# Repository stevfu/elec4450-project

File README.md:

# Custom Buck Converter 
My group designed a unidirectional buck converter with an active low-pass filter and control using a C2000 microcontroller.

The following specifications for this converter are: 

$$
V_i = 36\text{V} - 50\text{V}
$$

$$
V_o = 30\text{V}
$$

$$
f_{sw} = 10\text{kHz}
$$

$$
\Delta I_L = 0.3 I_L
$$

$$
\Delta V_o = 0.005 V_o
$$

The layout, schematic and PCB design of the buck converter was done in KiCAD.

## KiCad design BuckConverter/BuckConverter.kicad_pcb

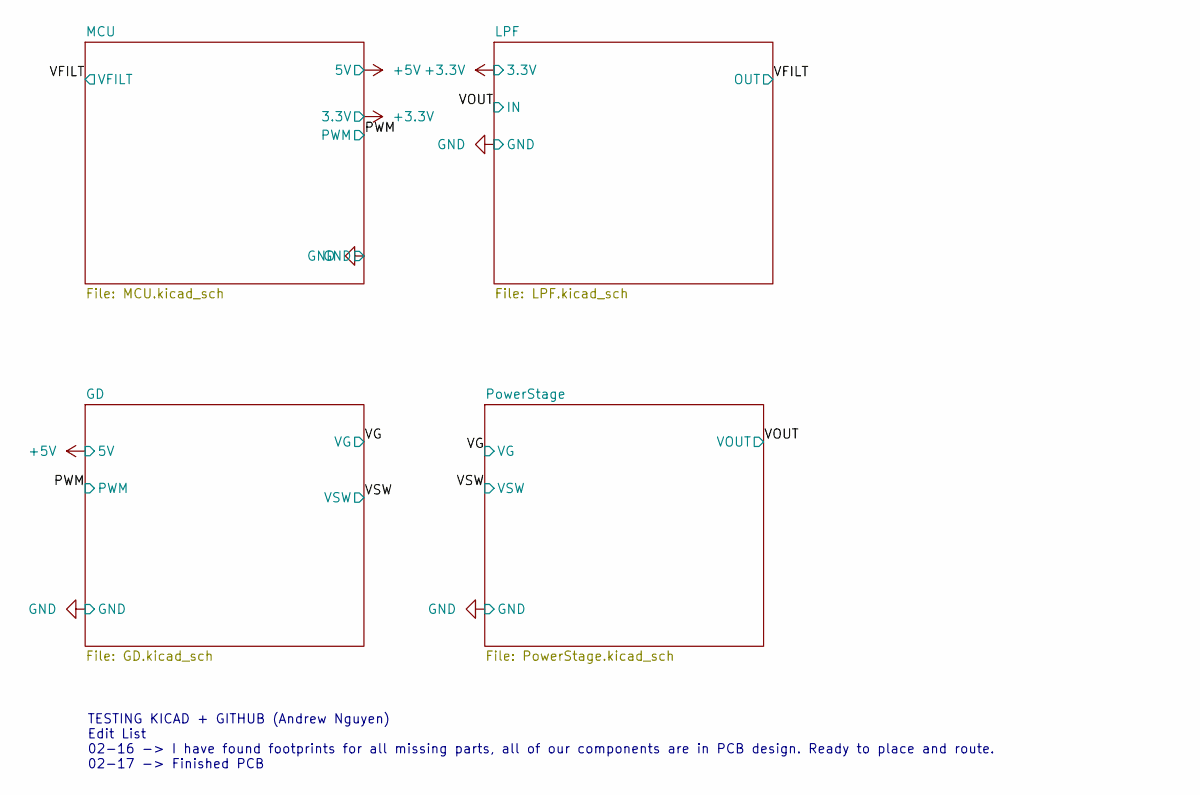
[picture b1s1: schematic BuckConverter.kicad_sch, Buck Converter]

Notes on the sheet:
TESTING KICAD + GITHUB (Andrew Nguyen) Edit List 02-16 -> I have found footprints for all missing parts, all of our components are in PCB design. Ready to place and route. 02-17 -> Finished PCB

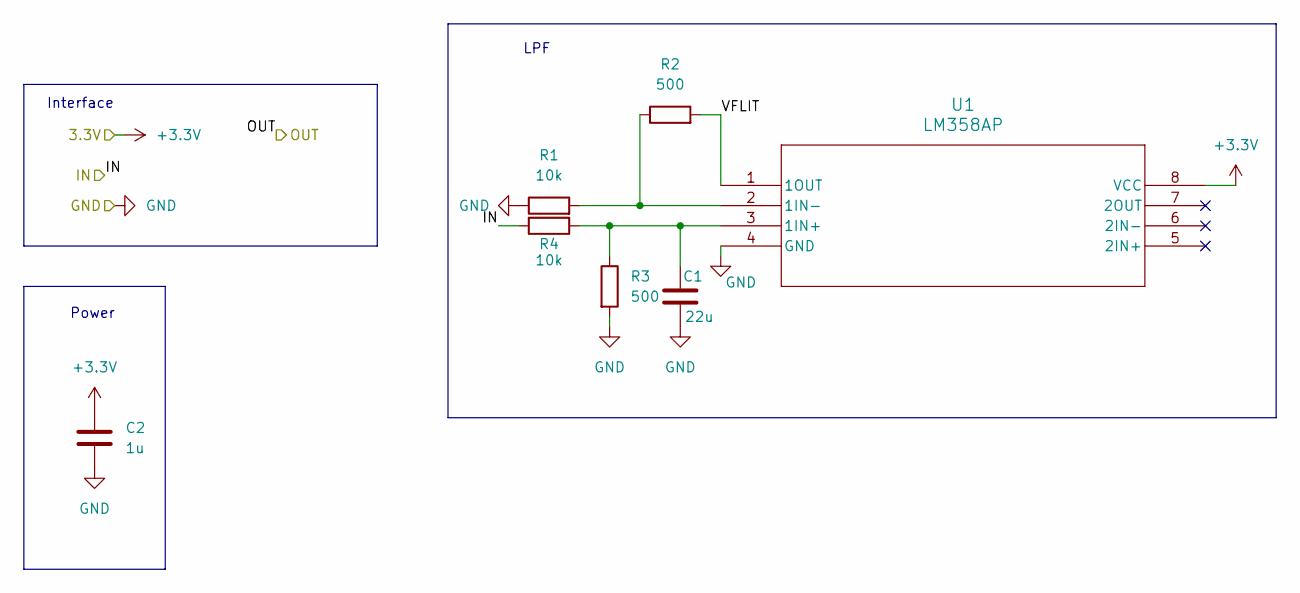
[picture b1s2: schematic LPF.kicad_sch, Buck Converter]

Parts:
C1: 22u; C_0805_2012Metric; Part Number C2012X5R1V226M125AC
C2: 1u; C_0805_2012Metric; Part Number TMCP1E105MTRF
R1, R4: 10k; R_0805_2012Metric; Part Number RMCF0805FT10K0
R2, R3: 500; R_0603_1608Metric; Part Number RT0603BRC07500RL
U1: LM358AP; P8; Part Number LM358AP

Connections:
+3.3V: C2.1, U1.8 (VCC); also elsewhere on the board
/LPF/VFLIT: R2.2, U1.1 (1OUT)
/VOUT: R4.2; also elsewhere on the board
GND: C1.2, C2.2, R1.1, R3.2, U1.4 (GND); also elsewhere on the board
unnamed: C1.1, R3.1, R4.1, U1.3 (1IN+)
unnamed: R1.2, R2.1, U1.2 (1IN-)

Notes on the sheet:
Power
Interface
LPF

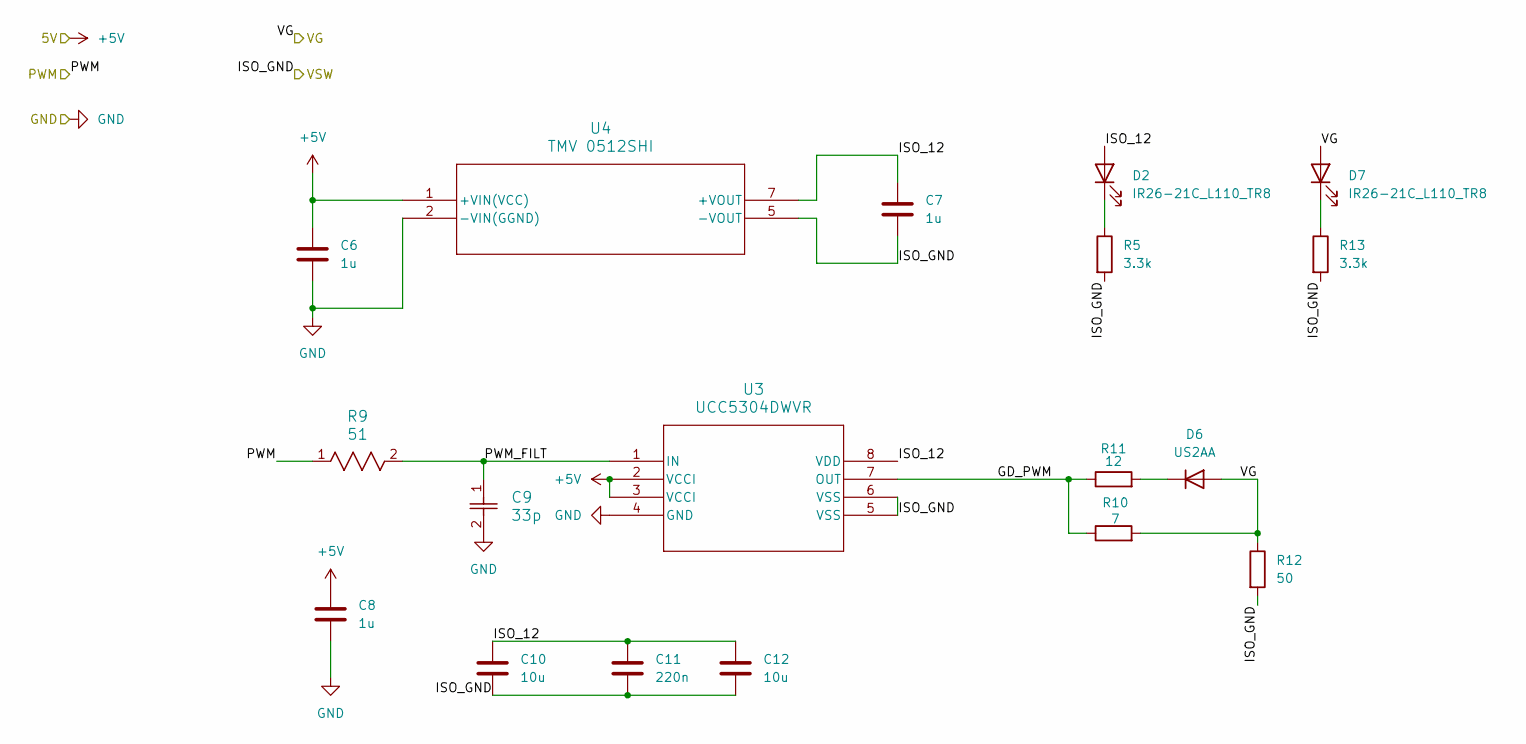
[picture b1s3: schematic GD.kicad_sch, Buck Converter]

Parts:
C6, C7: 1u; C_0805_2012Metric; Part Number TMCP1E105MTRF
C8: 1u; C_0805_2012Metric_Pad1.18x1.45mm_HandSolder; Part Number TMCP1E105MTRF
C9: 33p; CAP_600F0R1AT250T_ATC; Part Number 600F330FT250XT
C10: 10u; C_0805_2012Metric; Part Number F951C106MPAAQ2
C11: 220n; C_0805_2012Metric; Part Number C0805C224K5RACTU
C12: 10u; C_0805_2012Metric; Part Number GRM21BR61E106KA73L
D2, D7: IR26-21C_L110_TR8; LED_1206_3216Metric; Part Number IR26-21C_L110_TR8
D6: US2AA; D_SMA; Part Number US2AA
R5, R13: 3.3k; R_0805_2012Metric_Pad1.20x1.40mm_HandSolder; Part Number ERU-P06F3301V
R9: 51; RC0805N_YAG; Part Number RC0805FR-0751RL
R10: 7; R_0805_2012Metric_Pad1.20x1.40mm_HandSolder; Part Number CRCW08057R15FKEA
R11: 12; R_0805_2012Metric_Pad1.20x1.40mm_HandSolder; Part Number RC0805FR-0712RL
R12: 50; R_1206_3216Metric_Pad1.30x1.75mm_HandSolder; Part Number RCP1206W50R0JTP
U3: UCC5304DWVR; SOIC8_DWV_TEX; Part Number UCC5304DWVR
U4: TMV 0512SHI; TMV-HI_SINGLE_TRP; Part Number TMV 0512SHI

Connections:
+5V: C6.1, C8.1, U3.2 (VCCI), U3.3 (VCCI), U4.1 (+VIN(VCC)); also elsewhere on the board
/GD/GD_PWM: R10.1, R11.1, U3.7 (OUT)
/GD/ISO_12: C7.1, C10.1, C11.1, C12.1, D2.2 (A), U3.8 (VDD), U4.7 (+VOUT)
/GD/PWM_FILT: C9.1, R9.2, U3.1 (IN)
/PWM: R9.1; also elsewhere on the board
/VG: D6.2 (A), D7.2 (A), R10.2, R12.1; also elsewhere on the board
/VSW: C7.2, C10.2, C11.2, C12.2, R5.2, R12.2, R13.2, U3.5 (VSS), U3.6 (VSS), U4.5 (-VOUT); also elsewhere on the board
GND: C6.2, C8.2, C9.2, U3.4 (GND), U4.2 (-VIN(GGND)); also elsewhere on the board
unnamed: D2.1 (K), R5.1
unnamed: D6.1 (K), R11.2
unnamed: D7.1 (K), R13.1

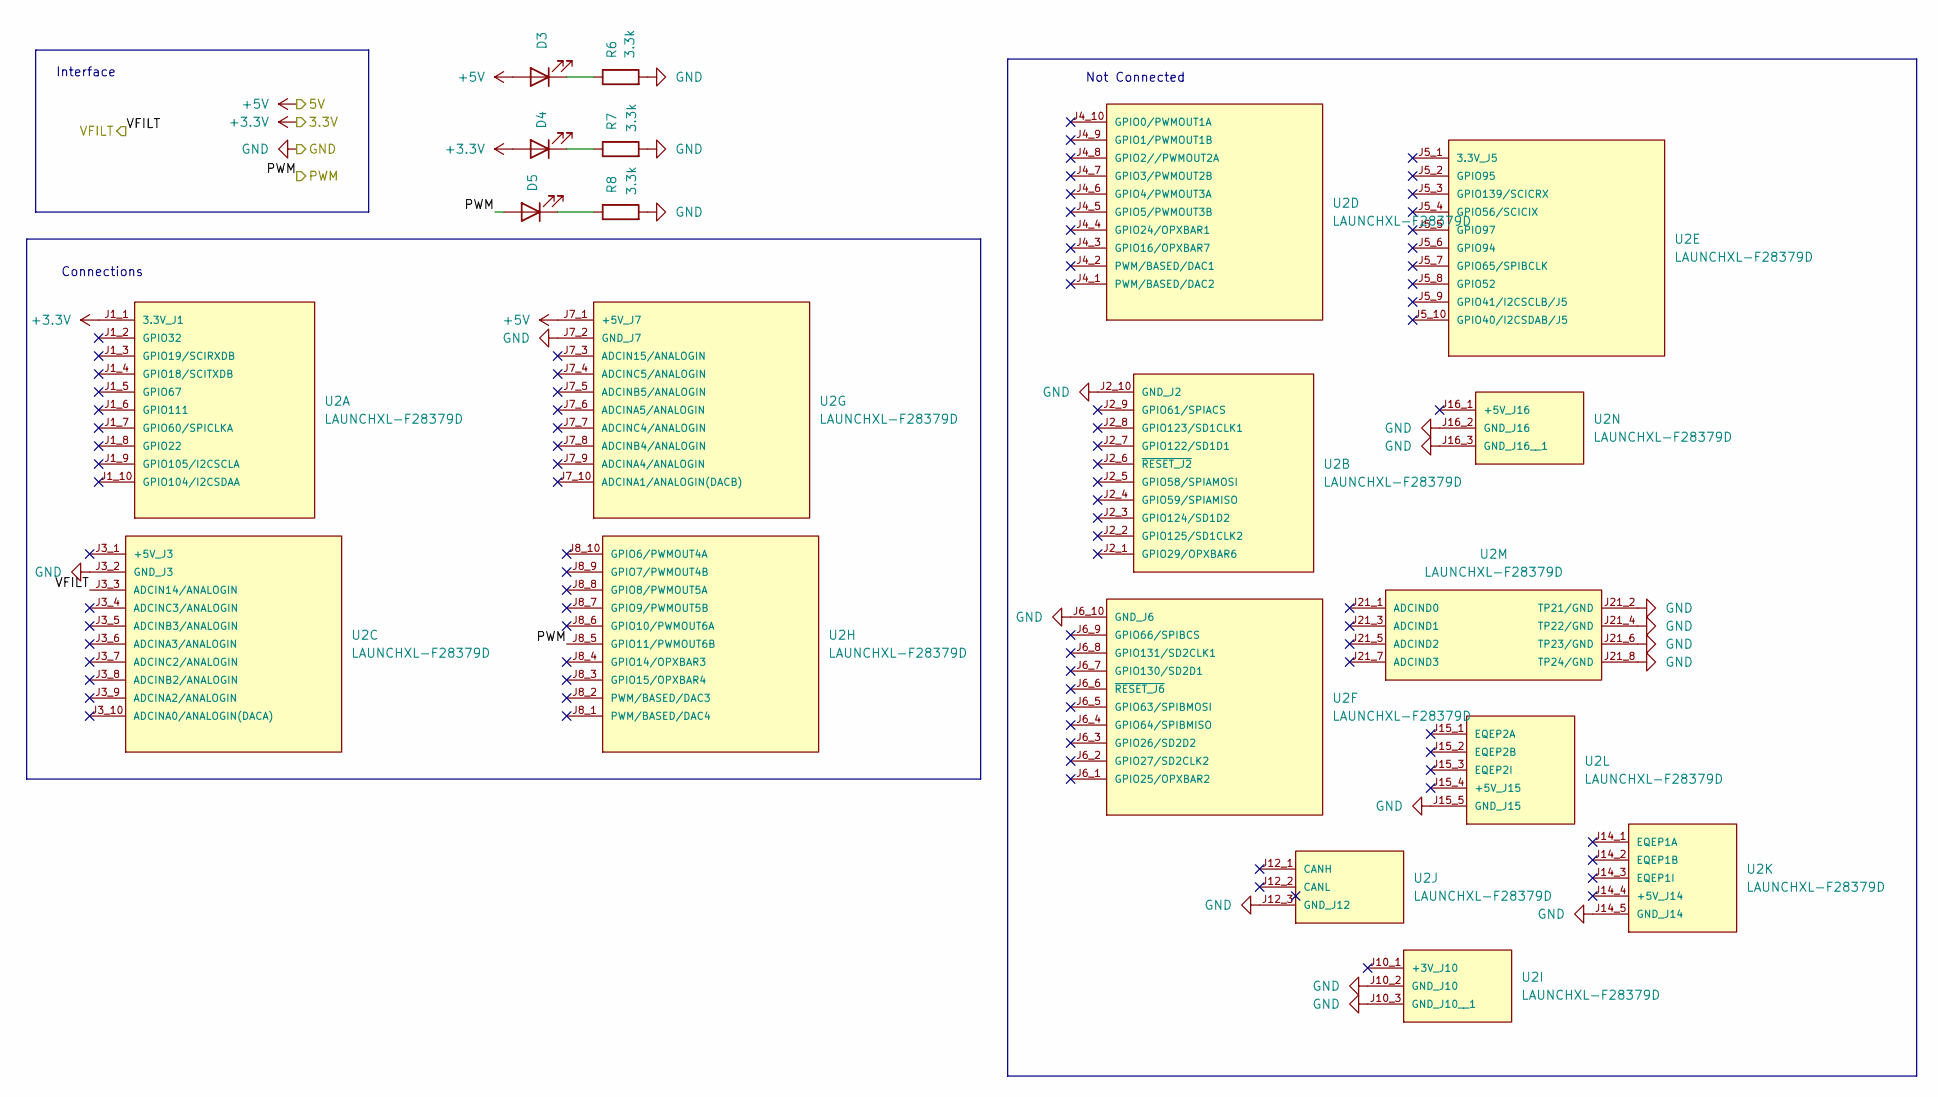
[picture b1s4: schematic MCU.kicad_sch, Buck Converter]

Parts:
D3, D4, D5: IR26-21C_L110_TR8; LED_1206_3216Metric; Part Number IR26-21C_L110_TR8
R6, R7, R8: 3.3k; R_0805_2012Metric_Pad1.20x1.40mm_HandSolder; Part Number ERU-P06F3301V
U2: LAUNCHXL-F28379D; MOD_LAUNCHXL-F28379D; PARTREV 2.0

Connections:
+3.3V: D4.2 (A), U2.J1_1 (3.3V_J1); also elsewhere on the board
+5V: D3.2 (A), U2.J7_1 (+5V_J7); also elsewhere on the board
/PWM: D5.2 (A), U2.J8_5 (GPIO11/PWMOUT6B); also elsewhere on the board
/VFILT: U2.J3_3 (ADCIN14/ANALOGIN)
GND: R6.2, R7.2, R8.2, U2.J2_10 (GND_J2), U2.J3_2 (GND_J3), U2.J6_10 (GND_J6), U2.J7_2 (GND_J7), U2.J10_2 (GND_J10), U2.J10_3 (GND_J10__1), U2.J12_3 (GND_J12), U2.J14_5 (GND_J14), U2.J15_5 (GND_J15), U2.J16_2 (GND_J16), U2.J16_3 (GND_J16__1), U2.J21_2 (TP21/GND), U2.J21_4 (TP22/GND), U2.J21_6 (TP23/GND), U2.J21_8 (TP24/GND); also elsewhere on the board
unnamed: D3.1 (K), R6.1
unnamed: D4.1 (K), R7.1
unnamed: D5.1 (K), R8.1

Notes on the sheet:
Not Connected
Connections
Interface

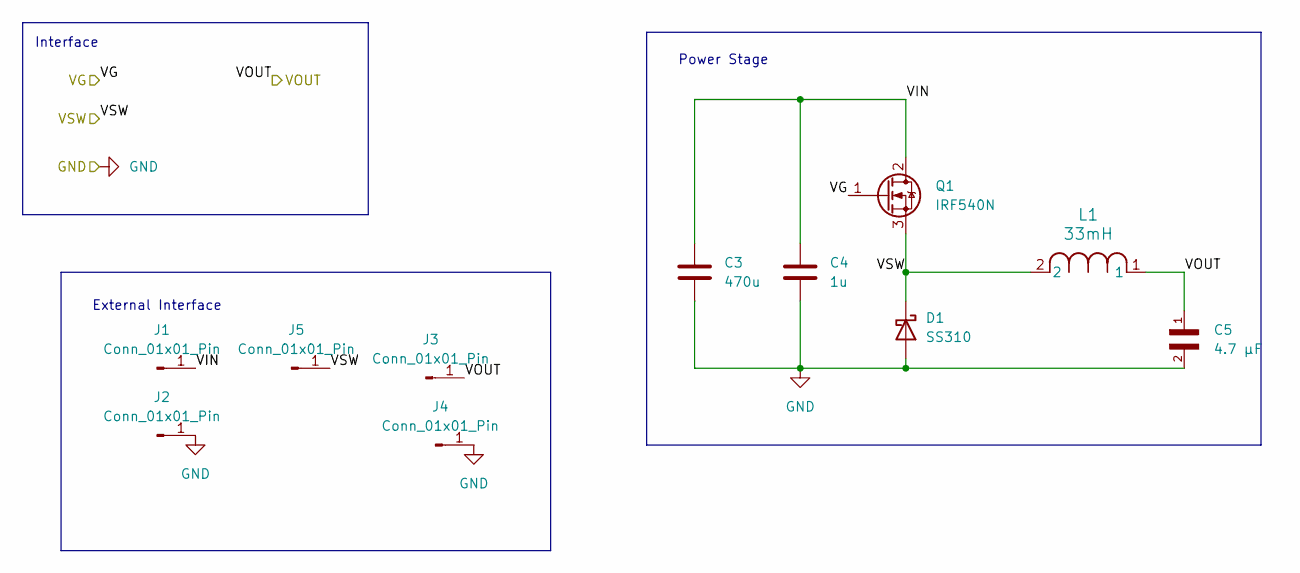
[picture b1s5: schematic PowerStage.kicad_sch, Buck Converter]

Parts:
C3: 470u; CP_Radial_D18.0mm_P7.50mm; Part Number 100ZLH470MEFC16X31.5
C4: 1u; C_0805_2012Metric_Pad1.18x1.45mm_HandSolder; Part Number GRM21BC72A105KE01L
C5: 4.7 µF; CAPC3216X190N; Part Number GRM31CC72A475KE11L
D1: SS310; D_SMA; Part Number SS310
J1, J2, J3, J4, J5: Conn_01x01_Pin; Banana_Jack_1Pin; Part Number BU-P72930
L1: 33mH; IND_BOURNS_5900; Part Number 5900-333-RC
Q1: IRF540N; TO-220-3_Vertical; Part Number IRF540N

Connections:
/PowerStage/VIN: C3.1, C4.1, J1.1, Q1.2 (D)
/VG: Q1.1 (G); also elsewhere on the board
/VOUT: C5.1, J3.1, L1.1; also elsewhere on the board
/VSW: D1.1 (K), J5.1, L1.2, Q1.3 (S); also elsewhere on the board
GND: C3.2, C4.2, C5.2, D1.2 (A), J2.1, J4.1; also elsewhere on the board

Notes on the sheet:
External Interface
Power Stage
Interface

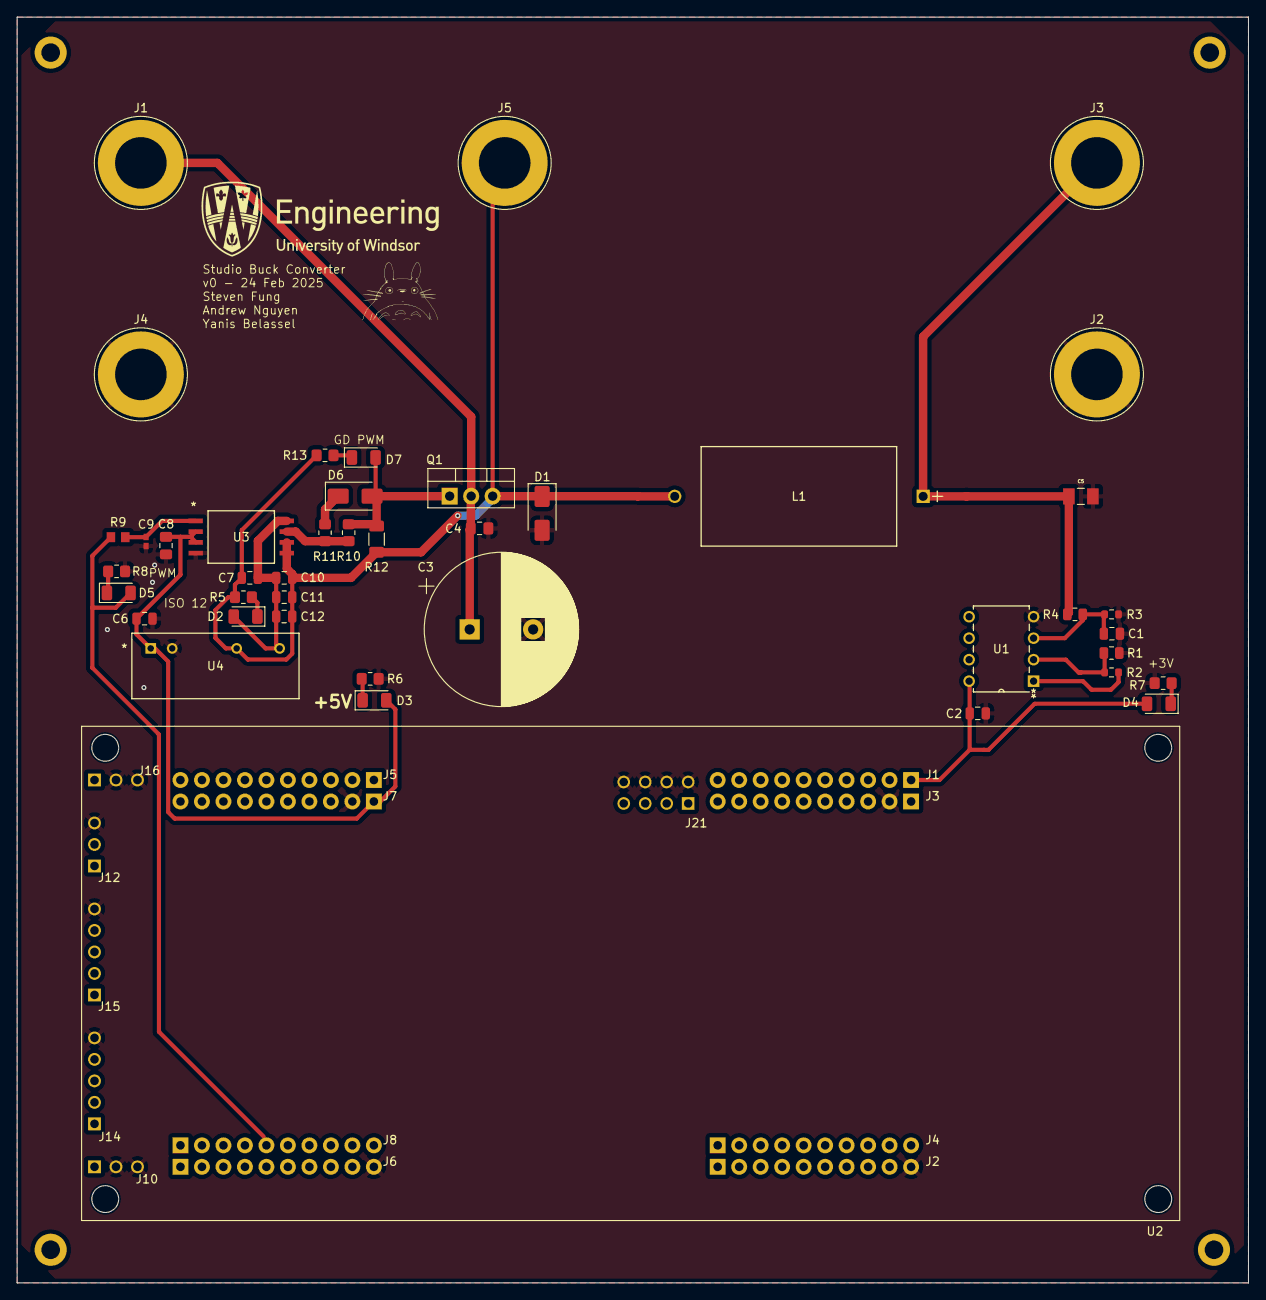
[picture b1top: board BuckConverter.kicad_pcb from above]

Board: 2 copper layers, 145.5 x 149.6 mm, 43 parts (0 on the bottom side), 20 nets.

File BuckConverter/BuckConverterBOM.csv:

Reference,Value,Qty,Part Number
C5,4.7 µF,1,GRM31CC72A475KE11L
L1,33mH,1,5900-333-RC
U1,LM358AP,1,LM358AP
U2,LAUNCHXL-F28379D,1,LAUNCHXL-F28379D
U3,UCC5304DWVR,1,UCC5304DWVR
D1,SS310,1,SS310
Q1,IRF540N,1,IRF540N
D6,US2AA,1,US2AA
C9,33p,1,600F330FT250XT
"D2,D3,D4,D5,D7",IR26-21C_L110_TR8,5,IR26-21C_L110_TR8
C11,220n,1,C0805C224K5RACTU
C12,10u,1,GRM21BR61E106KA73L
C3,470u,1,100ZLH470MEFC16X31.5
"J1,J2,J3,J4,J5",Conn_01x01_Pin,5,BU-P72930
R9,51,1,RC0805FR-0751RL
"R1,R4",10k,2,RMCF0805FT10K0
"R2,R3",500,2,RT0603BRC07500RL
"R5,R6,R7,R8,R13",3.3k,5,ERU-P06F3301V
R10,7,1,CRCW08057R15FKEA
R11,12,1,RC0805FR-0712RL
R12,50,1,RCP1206W50R0JTP
"C2,C6,C7,C8",1u,4,TMCP1E105MTRF
U4,TMV 0512SHI,1,TMV 0512SHI
C1,22u,1,C2012X5R1V226M125AC
C4,1u,1,GRM21BC72A105KE01L
C10,10u,1,F951C106MPAAQ2
Heatsink,,1,577202B00000G
Standoffs,,4,971100244
MCU Connectors,,4,61202021621

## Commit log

2025-01-21 added base simulink file
2025-01-23 updated simulink model
2025-01-23 added testing.m
2025-02-02 updated buckConverter.slx
2025-02-02 Initial commit(Just schm so far)
2025-02-16 Add all footprints
2025-02-18 PCB Completed
2025-02-20 basic simulink model done
2025-02-20 added controller to model and sisotool design
2025-02-20 controller design in simulink
2025-02-21 completed simulink model
2025-02-22 changed some simulation values
2025-02-22 added script for nice figures
2025-02-22 added Pictures folder
2025-02-22 added sample picture
2025-02-22 changed PI tuning script and values in sim
2025-02-22 LPF updates
2025-02-22 pcb name printed
2025-02-22 PCB updated LC footprints
2025-02-23 PCB Final Draft
2025-02-23 Updated Plots Matlab Code
2025-02-24 updated BOM
2025-02-25 Added subtitle and y-axis labelling
2025-02-25 added BOM cvs
2025-02-25 Finalize
2025-02-25 removed fluff
2025-02-27 Added BOM to main tree
2025-03-03 Update PCB and BOM
2025-03-06 added picture of pcb
